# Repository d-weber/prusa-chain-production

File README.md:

# Prusa i3 MK3 Chain Production add-on

Add chain production capability to your Prusa i3

# How it works
- The arduino controls the steppers & fans
- The printer is controlled via octopi
- A [script](octoprint-plugin/main.py) on the octopi monitors the octoprint status and controls the arduino via usb-serial to start cooling and trigger the ejection

# Demo video

# Assembly Bill of materials
Most of the parts can be ordered on Aliexpress at a small cost, for a total of approx $100

Description | Count | Français | English
------------ | ------------- | ------------- | -------------
Nema 17 stepper | 2 | [AliExpress](https://fr.aliexpress.com/item/32572890101.html?spm=a2g0o.productlist.0.0.564c27b3pHR0G2&algo_pvid=abd5054d-e8d8-4ced-8ff2-9446c7aa35a8&algo_expid=abd5054d-e8d8-4ced-8ff2-9446c7aa35a8-3&btsid=0b0a050115944744286904328e9042&ws_ab_test=searchweb0_0,searchweb201602_,searchweb201603_) | [AliExpress](https://www.aliexpress.com/item/32572890101.html?spm=a2g0o.productlist.0.0.564c27b3pHR0G2&algo_pvid=abd5054d-e8d8-4ced-8ff2-9446c7aa35a8&algo_expid=abd5054d-e8d8-4ced-8ff2-9446c7aa35a8-3&btsid=0b0a050115944744286904328e9042&ws_ab_test=searchweb0_0,searchweb201602_,searchweb201603_)
350mm 2040 V-SLOT Aluminium profile | 2 | [AliExpress](https://fr.aliexpress.com/item/32920516912.html?spm=a2g0o.productlist.0.0.31a037cc8dbPGY&algo_pvid=9b46cb6c-e7bb-4b1c-9eaa-0ad6e82b1f00&algo_expid=9b46cb6c-e7bb-4b1c-9eaa-0ad6e82b1f00-0&btsid=0b0a050115944742227557785e9042&ws_ab_test=searchweb0_0,searchweb201602_,searchweb201603_) | [AliExpress](https://www.aliexpress.com/item/32920516912.html?spm=a2g0o.productlist.0.0.31a037cc8dbPGY&algo_pvid=9b46cb6c-e7bb-4b1c-9eaa-0ad6e82b1f00&algo_expid=9b46cb6c-e7bb-4b1c-9eaa-0ad6e82b1f00-0&btsid=0b0a050115944742227557785e9042&ws_ab_test=searchweb0_0,searchweb201602_,searchweb201603_)
300mm 2020 V-SLOT Aluminium profile | 1 | [AliExpress](https://fr.aliexpress.com/item/32998701000.html?spm=a2g0o.productlist.0.0.fc8950e06k5nl7&algo_pvid=6a9e8ca4-d213-479d-98c0-849f8f18575f&algo_expid=6a9e8ca4-d213-479d-98c0-849f8f18575f-5&btsid=0b0a050115944742630778856e9042&ws_ab_test=searchweb0_0,searchweb201602_,searchweb201603_) | [AliExpress](https://www.aliexpress.com/item/32998701000.html?spm=a2g0o.productlist.0.0.fc8950e06k5nl7&algo_pvid=6a9e8ca4-d213-479d-98c0-849f8f18575f&algo_expid=6a9e8ca4-d213-479d-98c0-849f8f18575f-5&btsid=0b0a050115944742630778856e9042&ws_ab_test=searchweb0_0,searchweb201602_,searchweb201603_)
Mini V-SLOT gantry | 2 | [AliExpress](https://fr.aliexpress.com/item/32984815098.html?spm=a2g0o.productlist.0.0.4c6e64e2MzCvUb&algo_pvid=5d87a2aa-0380-4a2a-86d2-979a4ea56efd&algo_expid=5d87a2aa-0380-4a2a-86d2-979a4ea56efd-3&btsid=0b0a0ae215944787701661018edb08&ws_ab_test=searchweb0_0,searchweb201602_,searchweb201603_) | [AliExpress](https://www.aliexpress.com/item/32984815098.html?spm=a2g0o.productlist.0.0.4c6e64e2MzCvUb&algo_pvid=5d87a2aa-0380-4a2a-86d2-979a4ea56efd&algo_expid=5d87a2aa-0380-4a2a-86d2-979a4ea56efd-3&btsid=0b0a0ae215944787701661018edb08&ws_ab_test=searchweb0_0,searchweb201602_,searchweb201603_)
Angle bracket for 2020 | 2 | [AliExpress](https://fr.aliexpress.com/item/4001050647146.html?spm=a2g0o.productlist.0.0.fc8950e06k5nl7&algo_pvid=6a9e8ca4-d213-479d-98c0-849f8f18575f&algo_expid=6a9e8ca4-d213-479d-98c0-849f8f18575f-11&btsid=0b0a050115944742630778856e9042&ws_ab_test=searchweb0_0,searchweb201602_,searchweb201603_) | [AliExpress](https://www.aliexpress.com/item/4001050647146.html?spm=a2g0o.productlist.0.0.fc8950e06k5nl7&algo_pvid=6a9e8ca4-d213-479d-98c0-849f8f18575f&algo_expid=6a9e8ca4-d213-479d-98c0-849f8f18575f-11&btsid=0b0a050115944742630778856e9042&ws_ab_test=searchweb0_0,searchweb201602_,searchweb201603_)
20T 6MM GT2 Idler pulley | 2 | [AliExpress](https://fr.aliexpress.com/item/32822906447.html?spm=a2g0o.productlist.0.0.284a2834HqTySR&algo_pvid=f88906f7-5095-4826-b755-d351980b6bfd&algo_expid=f88906f7-5095-4826-b755-d351980b6bfd-1&btsid=0b0a050115944745423665576e9042&ws_ab_test=searchweb0_0,searchweb201602_,searchweb201603_) | [AliExpress](https://www.aliexpress.com/item/32822906447.html?spm=a2g0o.productlist.0.0.284a2834HqTySR&algo_pvid=f88906f7-5095-4826-b755-d351980b6bfd&algo_expid=f88906f7-5095-4826-b755-d351980b6bfd-1&btsid=0b0a050115944745423665576e9042&ws_ab_test=searchweb0_0,searchweb201602_,searchweb201603_)
20T 6MM GT2 Motor pulley | 2 | [AliExpress](https://fr.aliexpress.com/item/4000640547601.html?spm=a2g0o.productlist.0.0.284a2834HqTySR&algo_pvid=f88906f7-5095-4826-b755-d351980b6bfd&algo_expid=f88906f7-5095-4826-b755-d351980b6bfd-0&btsid=0b0a050115944745423665576e9042&ws_ab_test=searchweb0_0,searchweb201602_,searchweb201603_) | [AliExpress](https://www.aliexpress.com/item/4000640547601.html?spm=a2g0o.productlist.0.0.284a2834HqTySR&algo_pvid=f88906f7-5095-4826-b755-d351980b6bfd&algo_expid=f88906f7-5095-4826-b755-d351980b6bfd-0&btsid=0b0a050115944745423665576e9042&ws_ab_test=searchweb0_0,searchweb201602_,searchweb201603_)
1M 6MM GT2 Belt | 2 | [AliExpress](https://fr.aliexpress.com/item/32853559638.html?spm=a2g0o.productlist.0.0.2c4a62c2EzoYBR&algo_pvid=9ca62668-b87c-4d73-b8c6-e6ab5b253c3b&algo_expid=9ca62668-b87c-4d73-b8c6-e6ab5b253c3b-1&btsid=0b0a050115944746279536894e9042&ws_ab_test=searchweb0_0,searchweb201602_,searchweb201603_) | [AliExpress](https://www.aliexpress.com/item/32853559638.html?spm=a2g0o.productlist.0.0.2c4a62c2EzoYBR&algo_pvid=9ca62668-b87c-4d73-b8c6-e6ab5b253c3b&algo_expid=9ca62668-b87c-4d73-b8c6-e6ab5b253c3b-1&btsid=0b0a050115944746279536894e9042&ws_ab_test=searchweb0_0,searchweb201602_,searchweb201603_)
120MM 12V FAN | 2 | [AliExpress](https://fr.aliexpress.com/item/33000978834.html?spm=a2g0o.productlist.0.0.b8fc338c62ssrr&algo_pvid=a35331b9-fa4b-49f0-97c6-582a7d75b8d1&algo_expid=a35331b9-fa4b-49f0-97c6-582a7d75b8d1-8&btsid=0b0a050115944750692027643e9042&ws_ab_test=searchweb0_0,searchweb201602_,searchweb201603_) | [AliExpress](https://www.aliexpress.com/item/33000978834.html?spm=a2g0o.productlist.0.0.b8fc338c62ssrr&algo_pvid=a35331b9-fa4b-49f0-97c6-582a7d75b8d1&algo_expid=a35331b9-fa4b-49f0-97c6-582a7d75b8d1-8&btsid=0b0a050115944750692027643e9042&ws_ab_test=searchweb0_0,searchweb201602_,searchweb201603_)
TMC2130 SPI StepStick | 2 | [AliExpress](https://fr.aliexpress.com/item/32970150483.html?spm=a2g0o.productlist.0.0.72ea1eb7ryF9Z0&algo_pvid=f6794725-60ea-4f19-8894-552e24a461bd&algo_expid=f6794725-60ea-4f19-8894-552e24a461bd-1&btsid=0b0a050115944751235671454e9042&ws_ab_test=searchweb0_0,searchweb201602_,searchweb201603_) | [AliExpress](https://www.aliexpress.com/item/32970150483.html?spm=a2g0o.productlist.0.0.72ea1eb7ryF9Z0&algo_pvid=f6794725-60ea-4f19-8894-552e24a461bd&algo_expid=f6794725-60ea-4f19-8894-552e24a461bd-1&btsid=0b0a050115944751235671454e9042&ws_ab_test=searchweb0_0,searchweb201602_,searchweb201603_)
Arduino pro micro clone | 2 | [AliExpress](https://fr.aliexpress.com/item/32902569443.html?spm=a2g0o.productlist.0.0.54762563pNu99P&algo_pvid=0173235d-81de-44fa-8d78-6d86316b9cff&algo_expid=0173235d-81de-44fa-8d78-6d86316b9cff-0&btsid=0b0a050115944751023318586e9042&ws_ab_test=searchweb0_0,searchweb201602_,searchweb201603_) | [AliExpress](https://www.aliexpress.com/item/32902569443.html?spm=a2g0o.productlist.0.0.54762563pNu99P&algo_pvid=0173235d-81de-44fa-8d78-6d86316b9cff&algo_expid=0173235d-81de-44fa-8d78-6d86316b9cff-0&btsid=0b0a050115944751023318586e9042&ws_ab_test=searchweb0_0,searchweb201602_,searchweb201603_)
M4x10 HEX Screw | 50 | [AliExpress](https://fr.aliexpress.com/item/10000150053486.html?spm=a2g0o.productlist.0.0.5ccf318eCvy3d4&algo_pvid=d198149e-e626-4c57-85f7-a98fd79f0d91&algo_expid=d198149e-e626-4c57-85f7-a98fd79f0d91-0&btsid=0b0a050115944747937261478e9042&ws_ab_test=searchweb0_0,searchweb201602_,searchweb201603_) | [AliExpress](https://www.aliexpress.com/item/10000150053486.html?spm=a2g0o.productlist.0.0.5ccf318eCvy3d4&algo_pvid=d198149e-e626-4c57-85f7-a98fd79f0d91&algo_expid=d198149e-e626-4c57-85f7-a98fd79f0d91-0&btsid=0b0a050115944747937261478e9042&ws_ab_test=searchweb0_0,searchweb201602_,searchweb201603_)
M5x30 HEX Screw | 2 | [AliExpress](https://fr.aliexpress.com/item/10000150053486.html?spm=a2g0o.productlist.0.0.5ccf318eCvy3d4&algo_pvid=d198149e-e626-4c57-85f7-a98fd79f0d91&algo_expid=d198149e-e626-4c57-85f7-a98fd79f0d91-0&btsid=0b0a050115944747937261478e9042&ws_ab_test=searchweb0_0,searchweb201602_,searchweb201603_) | [AliExpress](https://www.aliexpress.com/item/10000150053486.html?spm=a2g0o.productlist.0.0.5ccf318eCvy3d4&algo_pvid=d198149e-e626-4c57-85f7-a98fd79f0d91&algo_expid=d198149e-e626-4c57-85f7-a98fd79f0d91-0&btsid=0b0a050115944747937261478e9042&ws_ab_test=searchweb0_0,searchweb201602_,searchweb201603_)
M5x50 HEX Screw | 2 | [AliExpress](https://fr.aliexpress.com/item/10000150053486.html?spm=a2g0o.productlist.0.0.5ccf318eCvy3d4&algo_pvid=d198149e-e626-4c57-85f7-a98fd79f0d91&algo_expid=d198149e-e626-4c57-85f7-a98fd79f0d91-0&btsid=0b0a050115944747937261478e9042&ws_ab_test=searchweb0_0,searchweb201602_,searchweb201603_) | [AliExpress](https://www.aliexpress.com/item/10000150053486.html?spm=a2g0o.productlist.0.0.5ccf318eCvy3d4&algo_pvid=d198149e-e626-4c57-85f7-a98fd79f0d91&algo_expid=d198149e-e626-4c57-85f7-a98fd79f0d91-0&btsid=0b0a050115944747937261478e9042&ws_ab_test=searchweb0_0,searchweb201602_,searchweb201603_)
M4x30 HEX Screw | 4 | [AliExpress](https://fr.aliexpress.com/item/10000150053486.html?spm=a2g0o.productlist.0.0.5ccf318eCvy3d4&algo_pvid=d198149e-e626-4c57-85f7-a98fd79f0d91&algo_expid=d198149e-e626-4c57-85f7-a98fd79f0d91-0&btsid=0b0a050115944747937261478e9042&ws_ab_test=searchweb0_0,searchweb201602_,searchweb201603_) | [AliExpress](https://www.aliexpress.com/item/10000150053486.html?spm=a2g0o.productlist.0.0.5ccf318eCvy3d4&algo_pvid=d198149e-e626-4c57-85f7-a98fd79f0d91&algo_expid=d198149e-e626-4c57-85f7-a98fd79f0d91-0&btsid=0b0a050115944747937261478e9042&ws_ab_test=searchweb0_0,searchweb201602_,searchweb201603_)
M4 NyLock Nut | 4 | [AliExpress](https://fr.aliexpress.com/item/32988995881.html?spm=a2g0o.productlist.0.0.48232c4bPHXJNh&algo_pvid=73bb6ea1-7038-4d8f-aa89-69344eaf84de&algo_expid=73bb6ea1-7038-4d8f-aa89-69344eaf84de-0&btsid=0b0a050115944749183954103e9042&ws_ab_test=searchweb0_0,searchweb201602_,searchweb201603_) | [AliExpress](https://www.aliexpress.com/item/32988995881.html?spm=a2g0o.productlist.0.0.48232c4bPHXJNh&algo_pvid=73bb6ea1-7038-4d8f-aa89-69344eaf84de&algo_expid=73bb6ea1-7038-4d8f-aa89-69344eaf84de-0&btsid=0b0a050115944749183954103e9042&ws_ab_test=searchweb0_0,searchweb201602_,searchweb201603_)
M4 2020 Nut | 50 | [AliExpress](https://fr.aliexpress.com/item/33043957747.html?spm=a2g0o.productlist.0.0.5dcc1b4fbfBnxe&algo_pvid=b122bcb7-951b-4d63-a89d-b83275a0bcb4&algo_expid=b122bcb7-951b-4d63-a89d-b83275a0bcb4-3&btsid=0b0a050115944748888203415e9042&ws_ab_test=searchweb0_0,searchweb201602_,searchweb201603_) | [AliExpress](https://www.aliexpress.com/item/33043957747.html?spm=a2g0o.productlist.0.0.5dcc1b4fbfBnxe&algo_pvid=b122bcb7-951b-4d63-a89d-b83275a0bcb4&algo_expid=b122bcb7-951b-4d63-a89d-b83275a0bcb4-3&btsid=0b0a050115944748888203415e9042&ws_ab_test=searchweb0_0,searchweb201602_,searchweb201603_)
M4 3030 Nut | 4 | [AliExpress](https://fr.aliexpress.com/item/33043957747.html?spm=a2g0o.productlist.0.0.5dcc1b4fbfBnxe&algo_pvid=b122bcb7-951b-4d63-a89d-b83275a0bcb4&algo_expid=b122bcb7-951b-4d63-a89d-b83275a0bcb4-3&btsid=0b0a050115944748888203415e9042&ws_ab_test=searchweb0_0,searchweb201602_,searchweb201603_) | [AliExpress](https://www.aliexpress.com/item/33043957747.html?spm=a2g0o.productlist.0.0.5dcc1b4fbfBnxe&algo_pvid=b122bcb7-951b-4d63-a89d-b83275a0bcb4&algo_expid=b122bcb7-951b-4d63-a89d-b83275a0bcb4-3&btsid=0b0a050115944748888203415e9042&ws_ab_test=searchweb0_0,searchweb201602_,searchweb201603_)

# Ejector PCB

Can be ordered through jlcpcb or any similar service

# Electronics Bill of materials
Description | Count | Français | English
------------ | ------------- | ------------- | -------------
TMC2130 SPI StepStick | 2 | [AliExpress](https://fr.aliexpress.com/item/32970150483.html?spm=a2g0o.productlist.0.0.72ea1eb7ryF9Z0&algo_pvid=f6794725-60ea-4f19-8894-552e24a461bd&algo_expid=f6794725-60ea-4f19-8894-552e24a461bd-1&btsid=0b0a050115944751235671454e9042&ws_ab_test=searchweb0_0,searchweb201602_,searchweb201603_) | [AliExpress](https://www.aliexpress.com/item/32970150483.html?spm=a2g0o.productlist.0.0.72ea1eb7ryF9Z0&algo_pvid=f6794725-60ea-4f19-8894-552e24a461bd&algo_expid=f6794725-60ea-4f19-8894-552e24a461bd-1&btsid=0b0a050115944751235671454e9042&ws_ab_test=searchweb0_0,searchweb201602_,searchweb201603_)
Arduino pro micro clone | 2 | [AliExpress](https://fr.aliexpress.com/item/32902569443.html?spm=a2g0o.productlist.0.0.54762563pNu99P&algo_pvid=0173235d-81de-44fa-8d78-6d86316b9cff&algo_expid=0173235d-81de-44fa-8d78-6d86316b9cff-0&btsid=0b0a050115944751023318586e9042&ws_ab_test=searchweb0_0,searchweb201602_,searchweb201603_) | [AliExpress](https://www.aliexpress.com/item/32902569443.html?spm=a2g0o.productlist.0.0.54762563pNu99P&algo_pvid=0173235d-81de-44fa-8d78-6d86316b9cff&algo_expid=0173235d-81de-44fa-8d78-6d86316b9cff-0&btsid=0b0a050115944751023318586e9042&ws_ab_test=searchweb0_0,searchweb201602_,searchweb201603_)

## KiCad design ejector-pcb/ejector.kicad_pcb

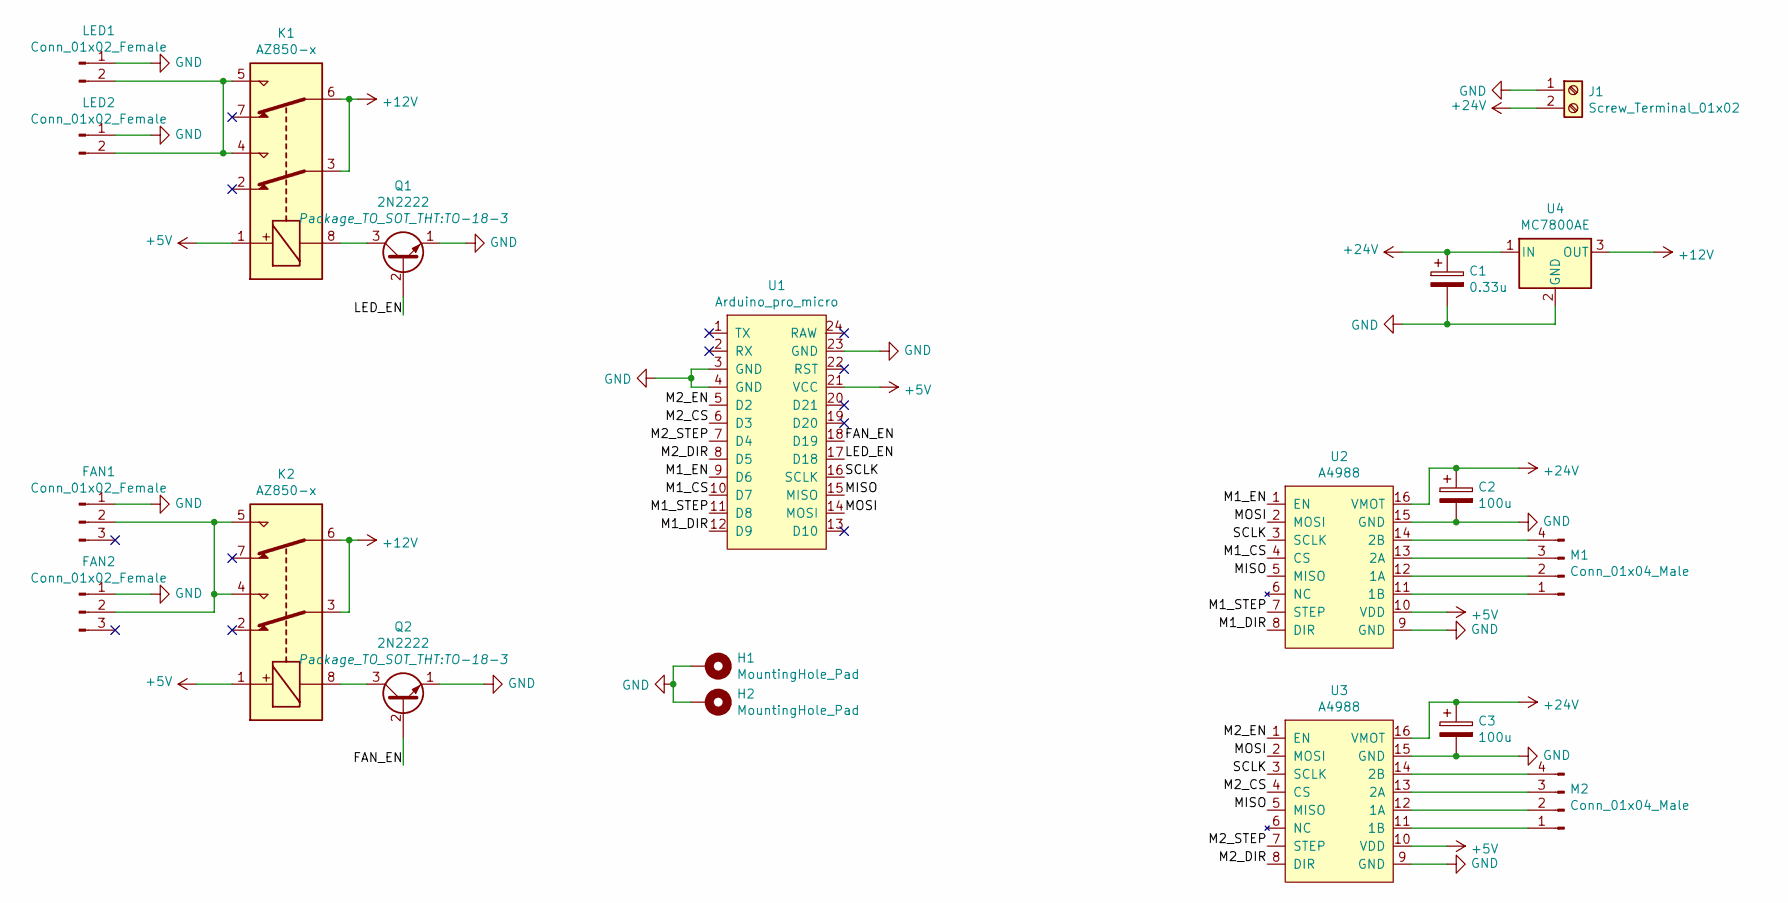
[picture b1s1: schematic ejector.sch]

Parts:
C1: 0.33u; CP_Radial_D5.0mm_P2.00mm
C2, C3: 100u; CP_Radial_D8.0mm_P3.50mm
FAN1, FAN2: Conn_01x02_Female; Molex_KK-254_AE-6410-03A_1x03_P2.54mm_Vertical
H1, H2: MountingHole_Pad; MountingHole_2.5mm_Pad
J1: Screw_Terminal_01x02; TerminalBlock_Phoenix_MKDS-1,5-2-5.08_1x02_P5.08mm_Horizont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
K1, K2: AZ850-x; Relay_DPDT_Panasonic_JW2
LED1, LED2: Conn_01x02_Female; Molex_SL_171971-0002_1x02_P2.54mm_Vertical
M1, M2: Conn_01x04_Male; PinHeader_1x04_P2.54mm_Vertical
Q1, Q2: 2N2222; TO-18-3
U1: Arduino_pro_micro; ARDUINOPROMICRO
U2, U3: A4988
U4: MC7800AE; TO-220-3_Horizontal_TabDown

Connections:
+5V: K1.1, K2.1, U1.21 (VCC), U2.10 (VDD), U3.10 (VDD)
+12V: K1.3, K1.6, K2.3, K2.6, U4.3 (OUT)
+24V: C1.1, C2.1, C3.1, J1.2, U2.16 (VMOT), U3.16 (VMOT), U4.1 (IN)
/FAN_EN: Q2.2 (B), U1.18 (D19)
/LED_EN: Q1.2 (B), U1.17 (D18)
/M1_CS: U1.10 (D7), U2.4 (CS)
/M1_DIR: U1.12 (D9), U2.8 (DIR)
/M1_EN: U1.9 (D6), U2.1 (EN)
/M1_STEP: U1.11 (D8), U2.7 (STEP)
/M2_CS: U1.6 (D3), U3.4 (CS)
/M2_DIR: U1.8 (D5), U3.8 (DIR)
/M2_EN: U1.5 (D2), U3.1 (EN)
/M2_STEP: U1.7 (D4), U3.7 (STEP)
/MISO: U1.15 (MISO), U2.5 (MISO), U3.5 (MISO)
/MOSI: U1.14 (MOSI), U2.2 (MOSI), U3.2 (MOSI)
/SCLK: U1.16 (SCLK), U2.3 (SCLK), U3.3 (SCLK)
GND: C1.2, C2.2, C3.2, FAN1.1, FAN2.1, H1.1, H2.1, J1.1, LED1.1, LED2.1, Q1.1 (E), Q2.1 (E), U1.3 (GND), U1.4 (GND), U1.23 (GND), U2.9 (GND), U2.15 (GND), U3.9 (GND), U3.15 (GND), U4.2 (GND)
unnamed: FAN1.2, FAN2.2, K2.4, K2.5
unnamed: K1.4, K1.5, LED1.2, LED2.2
unnamed: K1.8, Q1.3 (C)
unnamed: K2.8, Q2.3 (C)
unnamed: M1.1, U2.11 (1B)
unnamed: M1.2, U2.12 (1A)
unnamed: M1.3, U2.13 (2A)
unnamed: M1.4, U2.14 (2B)
unnamed: M2.1, U3.11 (1B)
unnamed: M2.2, U3.12 (1A)
unnamed: M2.3, U3.13 (2A)
unnamed: M2.4, U3.14 (2B)

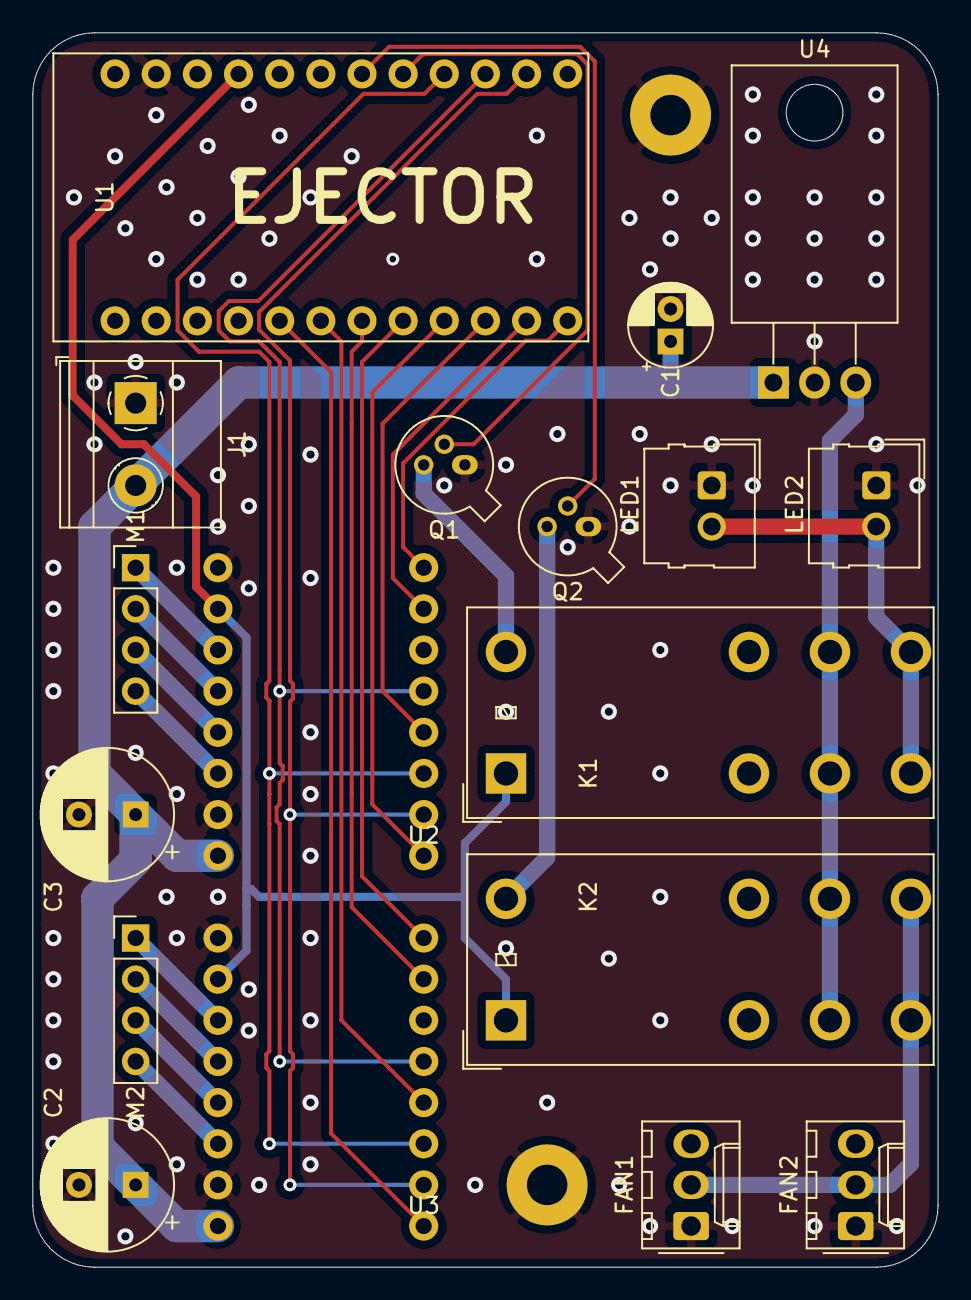
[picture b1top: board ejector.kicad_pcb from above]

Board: 2 copper layers, 55.9 x 76.2 mm, 20 parts (0 on the bottom side), 29 nets.

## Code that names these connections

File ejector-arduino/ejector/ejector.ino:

#include <TMCStepper.h>
#include <AccelStepper.h>
#define R_SENSE 0.11f
using namespace TMC2130_n;

// Serial commands
#define CMD_UNKNOWN 0
#define CMD_PING    1
#define CMD_HOME    2
#define CMD_END     3
#define CMD_EJECT   4
#define CMD_FAN_ON  5
#define CMD_FAN_OFF 6
#define CMD_LED_ON  7
#define CMD_LED_OFF 8
#define CMD_MOVE_FRONT 9
#define CMD_MOVE_REAR 10

// Motor 1
#define PIN_M1_ENABLE 6
#define PIN_M1_CS 7
#define PIN_M1_STEP 8
#define PIN_M1_DIR 9
TMC2130Stepper driverM1(PIN_M1_CS, R_SENSE);
AccelStepper stepperM1 = AccelStepper(AccelStepper::DRIVER, PIN_M1_STEP, PIN_M1_DIR);

// Motor 2
#define PIN_M2_ENABLE 2
#define PIN_M2_CS 3
#define PIN_M2_STEP 4
#define PIN_M2_DIR 5
TMC2130Stepper driverM2(PIN_M2_CS, R_SENSE);
AccelStepper stepperM2 = AccelStepper(AccelStepper::DRIVER, PIN_M2_STEP, PIN_M2_DIR);

// Other pins
#define PIN_LED 18
#define PIN_FAN 19

// Config
#define MICROSTEP 4
#define MAX_MOVING_TIME 10 // s
#define DEBUG false 
#define STEPS_PER_MM 5
#define STALL_VALUE 6
#define MAX_STALL 100

int maxPos = 280;
long mm2Step(long distance) {
  return  distance * STEPS_PER_MM * MICROSTEP;
}

long step2mm(long step) {
  return step / STEPS_PER_MM / MICROSTEP;
}

void setup() {
  Serial.begin(115200);

  // Fan & leds relays
  pinMode(PIN_LED, OUTPUT);
  pinMode(PIN_FAN, OUTPUT);
  pinMode(PIN_M1_CS, OUTPUT);
  pinMode(PIN_M2_CS, OUTPUT);

  while (!Serial) {
    ; // wait for serial port to connect. Needed for native USB
  }

  // Test relays
  digitalWrite(PIN_FAN, HIGH); 
  delay(1000);
  digitalWrite(PIN_FAN, LOW); 
  delay(500);
  digitalWrite(PIN_LED, HIGH); 
  delay(1000);
  digitalWrite(PIN_LED, LOW);

  // Enable SPI
  SPI.begin();
  pinMode(MISO, INPUT_PULLUP);

  // Init M1
  driverM1.begin();
  driverM1.rms_current(1000);
  driverM1.toff(4);
  driverM1.blank_time(24);
  driverM1.microsteps(MICROSTEP);
  driverM1.TCOOLTHRS(0xFFFFF); // 20bit max
  driverM1.THIGH(0);
  driverM1.semin(5);
  driverM1.semax(2);
  driverM1.sedn(0b01);
  driverM1.sgt(STALL_VALUE);
  driverM1.switchCSpin(LOW);
  stepperM1.setMaxSpeed(100 * MICROSTEP);
  stepperM1.setAcceleration(1000 * MICROSTEP);
  stepperM1.setEnablePin(PIN_M1_ENABLE);
  stepperM1.setPinsInverted(false, false, true);
  stepperM1.disableOutputs();

  // Init M2
  driverM2.begin();
  driverM2.rms_current(1000);
  driverM2.toff(4);
  driverM2.blank_time(24);
  driverM2.microsteps(MICROSTEP);
  driverM2.TCOOLTHRS(0xFFFFF); // 20bit max
  driverM2.THIGH(0);
  driverM2.semin(5);
  driverM2.semax(2);
  driverM2.sedn(0b01);
  driverM2.sgt(STALL_VALUE);
  driverM2.switchCSpin(LOW);
  stepperM2.setMaxSpeed(100 * MICROSTEP);
  stepperM2.setAcceleration(1000 * MICROSTEP);
  stepperM2.setEnablePin(PIN_M2_ENABLE);
  stepperM2.setPinsInverted(false, false, true);
  stepperM2.disableOutputs();
}

int parseStringCommand(String stringCommand) {
    if (stringCommand.equals("PING")) {
      return CMD_PING;
    } else if (stringCommand.equals("MOVE FRONT")) {
      return CMD_MOVE_FRONT;
    } else if (stringCommand.equals("MOVE REAR")) {
      return CMD_MOVE_REAR;
    } else if (stringCommand.equals("HOME")) {
      return CMD_HOME;
    } else if (stringCommand.equals("END")) {
      return CMD_END;
    } else if (stringCommand.equals("EJECT")) {
      return CMD_EJECT;
    } else if (stringCommand.equals("FAN ON")) {
      return CMD_FAN_ON;
    } else if (stringCommand.equals("FAN OFF")) {
      return CMD_FAN_OFF;
    } else if (stringCommand.equals("LED ON")) {
      return CMD_LED_ON;
    } else if (stringCommand.equals("LED OFF")) {
      return CMD_LED_OFF;
    } else {
      return CMD_UNKNOWN  ;
    }
}

int getM1StallValue() {
  DRV_STATUS_t drv_status{0};
  drv_status.sr = driverM1.DRV_STATUS();
  return drv_status.sg_result;
}

int getM2StallValue() {
  DRV_STATUS_t drv_status{0};
  drv_status.sr = driverM2.DRV_STATUS();
  return drv_status.sg_result;
}

long moveTo(long distance, long speed, bool sync = true) {
  stepperM1.setMaxSpeed(speed * MICROSTEP);
  stepperM2.setMaxSpeed(speed * MICROSTEP);
  stepperM1.moveTo(mm2Step(distance));
  stepperM2.moveTo(mm2Step(distance));
  uint32_t startTime = millis();
  uint32_t lastTime = millis();
  uint32_t lastStallCheck = millis();
  while(true) {
    stepperM1.run();
    stepperM2.run();

    if ((millis() - lastStallCheck) > 10) {
      lastStallCheck = millis();
      int M1StallValue = getM1StallValue();
      int M2StallValue = getM2StallValue();

      if ((millis() - startTime) > 100 && (M1StallValue < MAX_STALL || M2StallValue < MAX_STALL)){
        if (M1StallValue < MAX_STALL) {
          if (DEBUG) Serial.print("Stalled M1: ");
          if (DEBUG) Serial.println(M1StallValue, DEC);
          stepperM1.move(0);
          stepperM1.setSpeed(0);
        }
        if (M2StallValue < MAX_STALL) {
          if (DEBUG) Serial.print("Stalled M2: ");
          if (DEBUG) Serial.println(M2StallValue, DEC);
          stepperM2.move(0);
          stepperM2.setSpeed(0);
        }
        if (sync) {
          stepperM1.move(0);
          stepperM2.move(0);
          stepperM1.setSpeed(0);
          stepperM2.setSpeed(0);
        }
        break;
      }
    }

    if (!stepperM1.isRunning() && !stepperM2.isRunning()){
      break;
    }
  }

  long avgPos = (stepperM1.currentPosition() + stepperM2.currentPosition()) / 2;
  return step2mm(avgPos);
}

void eject() {
  stepperM1.enableOutputs();
  stepperM2.enableOutputs();

  // Deploy arm
  int pos = moveTo(70, 100);
  int i = 0;
  int speeds[] = {600, 500, 400, 300, 200};

  while (pos < maxPos * 0.95) {
    stepperM1.move(0);
    stepperM2.move(0);
    stepperM1.setSpeed(0);
    stepperM2.setSpeed(0);

    delay(500);
    moveTo(70, 500);
    delay(500);

    pos = moveTo(maxPos, speeds[i]);
    i++;
    if (i > 4) {
      i = 0;
    }
  }
  while (pos > 75) {
    pos  = moveTo(70, 500);
  }
  while (pos > 5) {
    pos  = moveTo(0, 100);
  }
  
  stepperM1.disableOutputs();
  stepperM2.disableOutputs();
}

void loop() {
  if (Serial.available() > 0) {
    String stringCommand = Serial.readStringUntil('\n');
    int command = parseStringCommand(stringCommand);
    switch (command) {
      case CMD_PING:
        Serial.println("PONG");
        break;
      case CMD_END:
        Serial.println("START");
        Serial.println("END");
        break;
      case CMD_EJECT:
        Serial.println("START");
        eject();
        Serial.println("END");
        break;
      case CMD_FAN_ON:
        digitalWrite(PIN_FAN, HIGH); 
        Serial.println("DONE");
        break;
      case CMD_FAN_OFF:
        digitalWrite(PIN_FAN, LOW); 
        Serial.println("DONE");
        break;
      case CMD_LED_ON:
        digitalWrite(PIN_LED, HIGH); 
        Serial.println("DONE");
        break;
      case CMD_LED_OFF:
        digitalWrite(PIN_LED, LOW); 
        Serial.println("DONE");
        break;
      default:
      case CMD_UNKNOWN:
        Serial.println("UNKNOWN COMMAND");
    }
  }
}

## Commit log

2020-07-11 Git init
2020-07-11 Update readme & license
2020-07-11 Rename LICENSE to LICENSE.md
2020-08-31 Add english Aliexpress URLs
2020-11-17 Add TMC2130 Support #2
2022-12-24 fix(docs): table formatting
